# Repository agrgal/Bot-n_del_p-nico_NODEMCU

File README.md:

# Botón del pánico. NodeMCU
Proyecto del Botón del pánico. NodeMCU

Este es mi primer proyecto con NodeMCU: un botón del pánico.

Consiste en dos dispositivos comunicados con el protocolo ESP-NOW. Cuando active un pulsador en uno, usado como estación, la información alcanza a otro, denominado central.

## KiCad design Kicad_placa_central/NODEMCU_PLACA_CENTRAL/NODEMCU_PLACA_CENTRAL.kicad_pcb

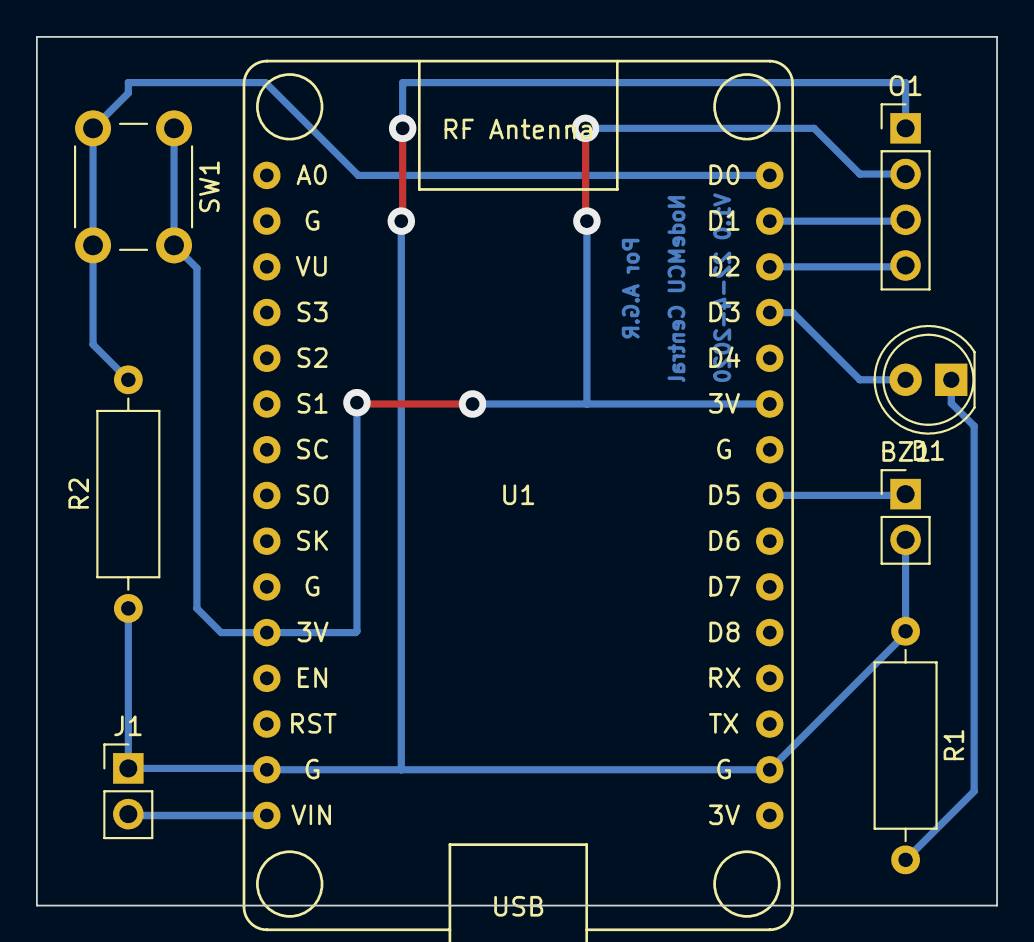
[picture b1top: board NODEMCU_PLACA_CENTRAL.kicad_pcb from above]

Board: 2 copper layers, 53.3 x 48.3 mm, 8 parts (0 on the bottom side), 9 nets.

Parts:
BZ1: Buzzer; PinHeader_1x02_P2.54mm_Vertical
D1: LED; LED_D5.0mm
J1: Conn_01x02_Female; PinHeader_1x02_P2.54mm_Vertical
O1: OLED; PinHeader_1x04_P2.54mm_Vertical
R1: 220; R_Axial_DIN0309_L9.0mm_D3.2mm_P12.70mm_Horizontal
R2: 10k; R_Axial_DIN0309_L9.0mm_D3.2mm_P12.70mm_Horizontal
SW1: SW_Push_Open_Dual_x2; SW_PUSH_6mm_H13mm
U1: NodeMCU1.0(ESP-12E); NodeMCU1.0(12-E)

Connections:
3_3V: O1.2, SW1.1, U1.11, U1.25
GND: BZ1.2, J1.1, O1.1, R1.1, R2.1, U1.14, U1.17
unnamed: BZ1.1, U1.23
unnamed: D1.1, R1.2
unnamed: D1.2, U1.27
unnamed: J1.2, U1.15
unnamed: O1.3, U1.29
unnamed: O1.4, U1.28
unnamed: R2.2, SW1.2, U1.30

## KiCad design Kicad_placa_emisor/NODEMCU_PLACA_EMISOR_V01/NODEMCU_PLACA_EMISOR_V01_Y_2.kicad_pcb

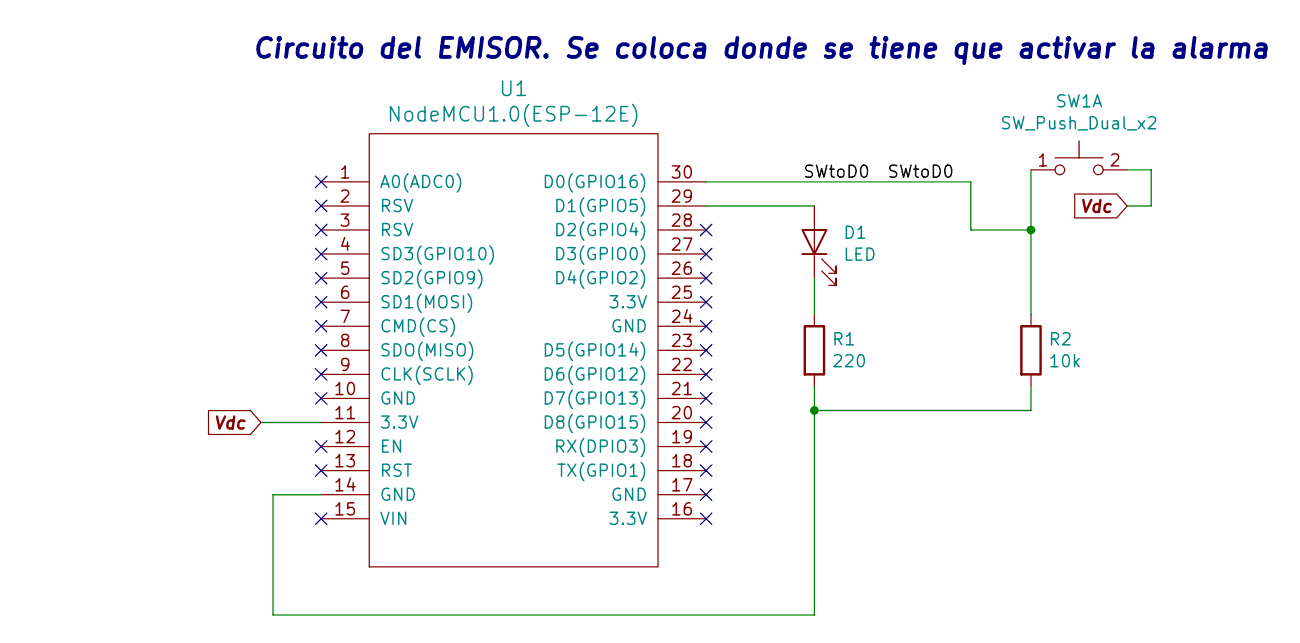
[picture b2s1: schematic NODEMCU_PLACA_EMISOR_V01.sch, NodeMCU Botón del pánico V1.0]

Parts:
D1: LED; LED_D5.0mm
R1: 220; R_Axial_DIN0411_L9.9mm_D3.6mm_P7.62mm_Vertical
R2: 10k; R_Axial_DIN0411_L9.9mm_D3.6mm_P7.62mm_Vertical
SW1: SW_Push_Dual_x2; SW_PUSH_6mm_H13mm
U1: NodeMCU1.0(ESP-12E); NodeMCU1.0(12-E)

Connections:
/SWtoD0: R2.1, SW1.1 (C), U1.30 (D0(GPIO16))
unnamed: D1.1 (K), R1.1
unnamed: D1.2 (A), U1.29 (D1(GPIO5))
unnamed: R1.2, R2.2, U1.14 (GND)
Vdc: SW1.2 (D), U1.11 (3.3V)

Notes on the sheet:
Circuito del EMISOR. Se coloca donde se tiene que activar la alarma

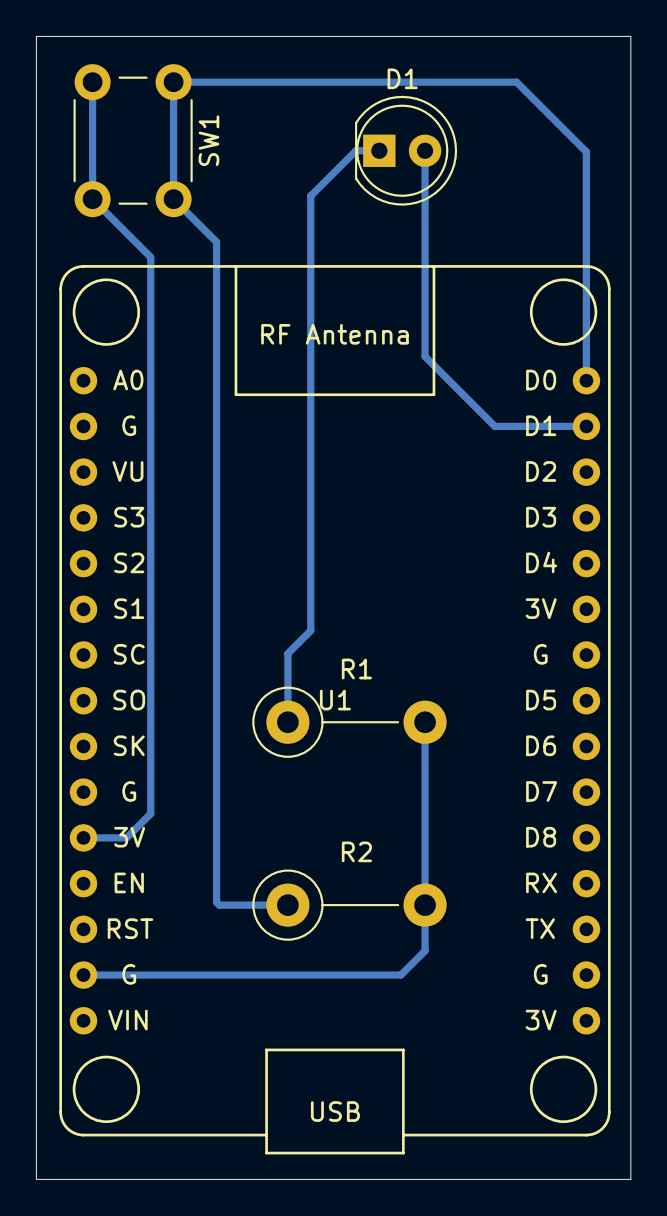
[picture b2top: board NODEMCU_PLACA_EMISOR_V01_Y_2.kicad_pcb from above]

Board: 2 copper layers, 33.0 x 63.5 mm, 5 parts (0 on the bottom side), 5 nets.

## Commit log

2020-04-22 Subida del proyecto BOTÓN DEL PÁNICO
2020-04-22 Añado programs y logos
